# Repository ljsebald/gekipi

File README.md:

# GekiPi

A controller for games such as O.N.G.E.K.I. based around the Raspberry Pi Pico.

Please note that this is still a Work-In-Progress and isn't really meant for
anyone to actually try to use just yet.

## License

The code in the firmware directory is covered by the MIT License. See
`COPYING.MIT` for more information.

The hardware design in the board directory is covered by the CERN Open Hardware
License Version 2 - Strongly Reciprocal (CERN-OHL-S). See `cern_ohl_s_v2.txt`
for more information.

## Dependencies

The firmware for GekiPi currently only depends on the base Raspberry Pi Pico
SDK, its TinyUSB library, and my version of pn532-lib (which is a git submodule
of the firmware directory).

## Pinouts and GPIO assignments:

Buttons (other than the WAD and Test/Service button) have the following pinout:
1. +5v
2. LED In
3. Signal (active low)
4. LED Out
5. GND

Test/Service have the following pinout:
1. Signal (active low)
2. GND

The WADs have the following pinout:
1. +5v
2. +3.3v
3. LED In
4. Signal (active high, +3.3v)
5. LED Out
6. GND

The NFC connector has the following pinout:
1. +5v
2. +3.3v
3. LED In
4. SDA
5. SCL
6. GND

The Stick connector has the following pinout:
1. +3.3v
2. Analog Signal
3. Analog GND

The LEDs are wired in the following order (all are single LEDs except the WADs):
1. Left Red
2. Left Green
3. Left Blue
4. Right Red
5. Right Green
6. Right Blue
7. Left Menu
8. Right Menu
9. Left WAD
10. Right WAD
11. NFC

The number of LEDs per WAD can be set in the code and defaults to 6.

GPIO pins are assigned as follows on the Pico:
- GPIO0: Left Red
- GPIO1: Left Green
- GPIO2: Left Blue
- GPIO3: Right Red
- GPIO4: Right Green
- GPIO5: Right Blue
- GPIO6: Left Menu
- GPIO7: Right Menu
- GPIO8: Left WAD
- GPIO9: Right WAD
- GPIO16: NFC SDA
- GPIO17: NFC SCL
- GPIO20: LED Output (to 74AHCT125, then Left Red)
- GPIO21: Service
- GPIO22: Test
- GPIO28/ADC2: Stick

All other ADC channels available on a standard Pi Pico board are wired to the
Analog connector (along with +3.3v and Analog GND).

All other GPIO pins (other than those on the Analog connector) are available on
the GPIO connector (along with +3.3v, +5v, and GND)

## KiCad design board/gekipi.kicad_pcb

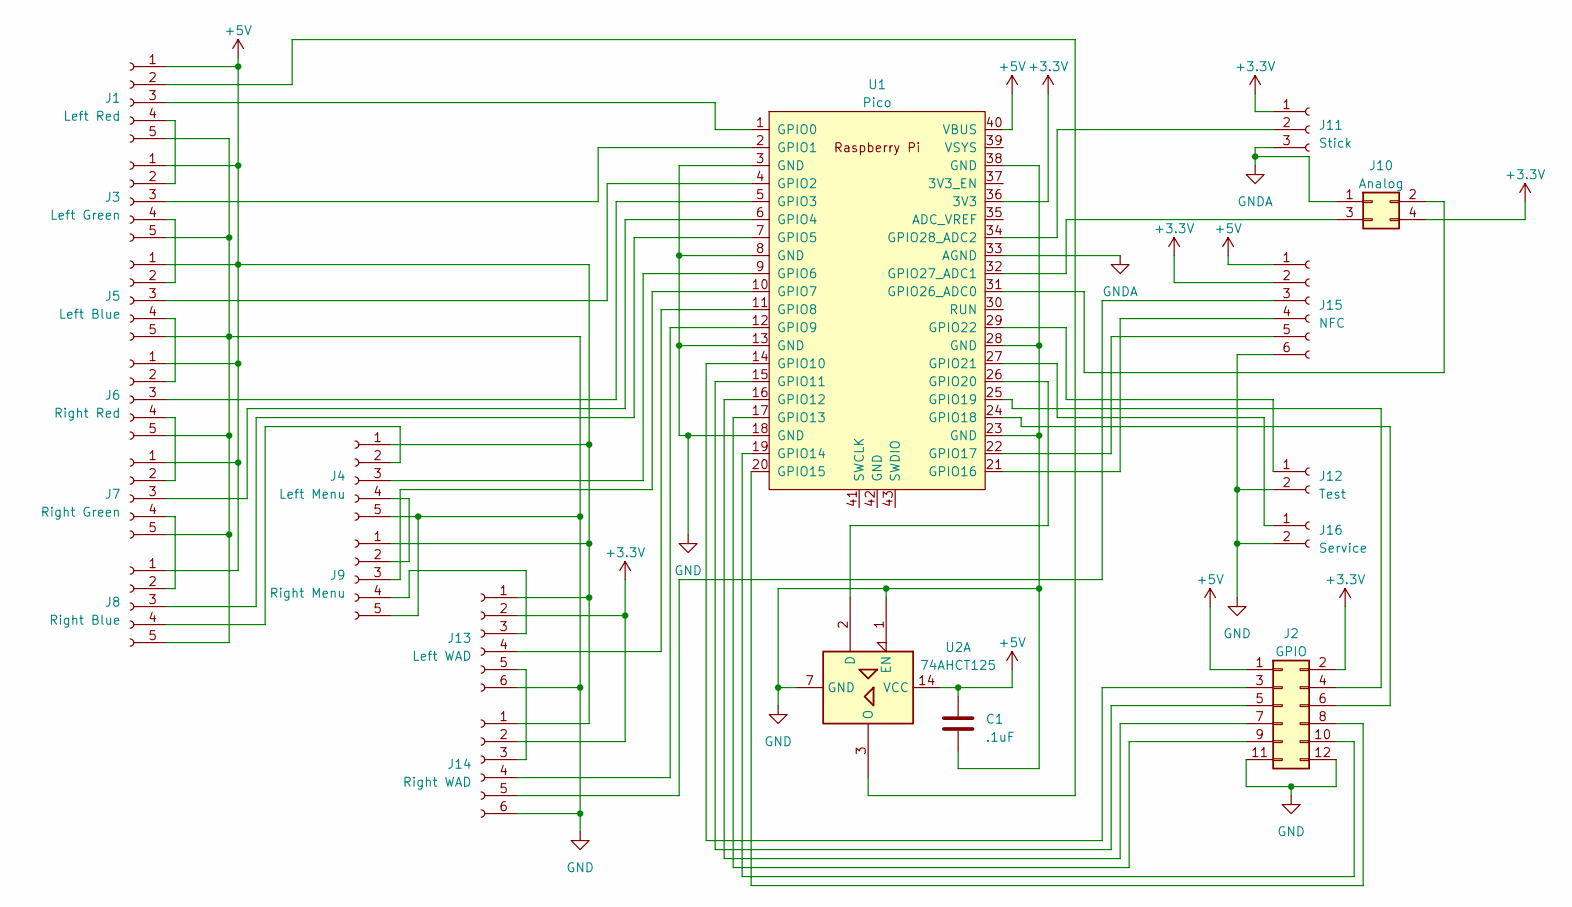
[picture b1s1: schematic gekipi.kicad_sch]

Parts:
C1: .1uF; C_Rect_L4.0mm_W2.5mm_P2.50mm
J1: Left Red; JST_XH_B5B-XH-A_1x05_P2.50mm_Vertical
J2: GPIO; PinHeader_2x06_P2.54mm_Vertical
J3: Left Green; JST_XH_B5B-XH-A_1x05_P2.50mm_Vertical
J4: Left Menu; JST_XH_B5B-XH-A_1x05_P2.50mm_Vertical
J5: Left Blue; JST_XH_B5B-XH-A_1x05_P2.50mm_Vertical
J6: Right Red; JST_XH_B5B-XH-A_1x05_P2.50mm_Vertical
J7: Right Green; JST_XH_B5B-XH-A_1x05_P2.50mm_Vertical
J8: Right Blue; JST_XH_B5B-XH-A_1x05_P2.50mm_Vertical
J9: Right Menu; JST_XH_B5B-XH-A_1x05_P2.50mm_Vertical
J10: Analog; PinHeader_2x02_P2.54mm_Vertical
J11: Stick; JST_XH_B3B-XH-A_1x03_P2.50mm_Vertical
J12: Test; JST_XH_B2B-XH-A_1x02_P2.50mm_Vertical
J13: Left WAD; JST_XH_B6B-XH-A_1x06_P2.50mm_Vertical
J14: Right WAD; JST_XH_B6B-XH-A_1x06_P2.50mm_Vertical
J15: NFC; JST_XH_B6B-XH-A_1x06_P2.50mm_Vertical
J16: Service; JST_XH_B2B-XH-A_1x02_P2.50mm_Vertical
U1: Pico; RPi_Pico_SMD_TH
U2: 74AHCT125; DIP-14_W7.62mm

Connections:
+3.3V: J2.2, J10.4, J11.1, J13.2, J14.2, J15.2, U1.36 (3V3)
+5V: C1.1, J1.1, J2.1, J3.1, J4.1, J5.1, J6.1, J7.1, J8.1, J9.1, J13.1, J14.1, J15.1, U1.40 (VBUS), U2.14 (VCC)
GND: C1.2, J1.5, J2.11, J2.12, J3.5, J4.5, J5.5, J6.5, J7.5, J8.5, J9.5, J12.2, J13.6, J14.6, J15.6, J16.2, U1.3 (GND), U1.8 (GND), U1.13 (GND), U1.18 (GND), U1.23 (GND), U1.28 (GND), U1.38 (GND), U2.1 (EN), U2.7 (GND)
GNDA: J10.1, J11.3, U1.33 (AGND)
unnamed: J1.2, U2.3 (O)
unnamed: J1.3, U1.1 (GPIO0)
unnamed: J1.4, J3.2
unnamed: J2.3, U1.14 (GPIO10)
unnamed: J2.4, U1.25 (GPIO19)
unnamed: J2.5, U1.15 (GPIO11)
unnamed: J2.6, U1.24 (GPIO18)
unnamed: J2.7, U1.16 (GPIO12)
unnamed: J2.8, U1.20 (GPIO15)
unnamed: J2.9, U1.17 (GPIO13)
unnamed: J2.10, U1.19 (GPIO14)
unnamed: J3.3, U1.2 (GPIO1)
unnamed: J3.4, J5.2
unnamed: J4.2, J8.4
unnamed: J4.3, U1.9 (GPIO6)
unnamed: J4.4, J9.2
unnamed: J5.3, U1.4 (GPIO2)
unnamed: J5.4, J6.2
unnamed: J6.3, U1.5 (GPIO3)
unnamed: J6.4, J7.2
unnamed: J7.3, U1.6 (GPIO4)
unnamed: J7.4, J8.2
unnamed: J8.3, U1.7 (GPIO5)
unnamed: J9.3, U1.10 (GPIO7)
unnamed: J10.2, U1.31 (GPIO26_ADC0)
unnamed: J10.3, U1.32 (GPIO27_ADC1)
unnamed: J11.2, U1.34 (GPIO28_ADC2)
unnamed: J12.1, U1.29 (GPIO22)
unnamed: J9.4, J13.3
unnamed: J13.4, U1.11 (GPIO8)
unnamed: J13.5, J14.3
unnamed: J14.4, U1.12 (GPIO9)
unnamed: J14.5, J15.3
unnamed: J15.4, U1.21 (GPIO16)
unnamed: J15.5, U1.22 (GPIO17)
unnamed: J16.1, U1.27 (GPIO21)
unnamed: U1.26 (GPIO20), U2.2 (D)

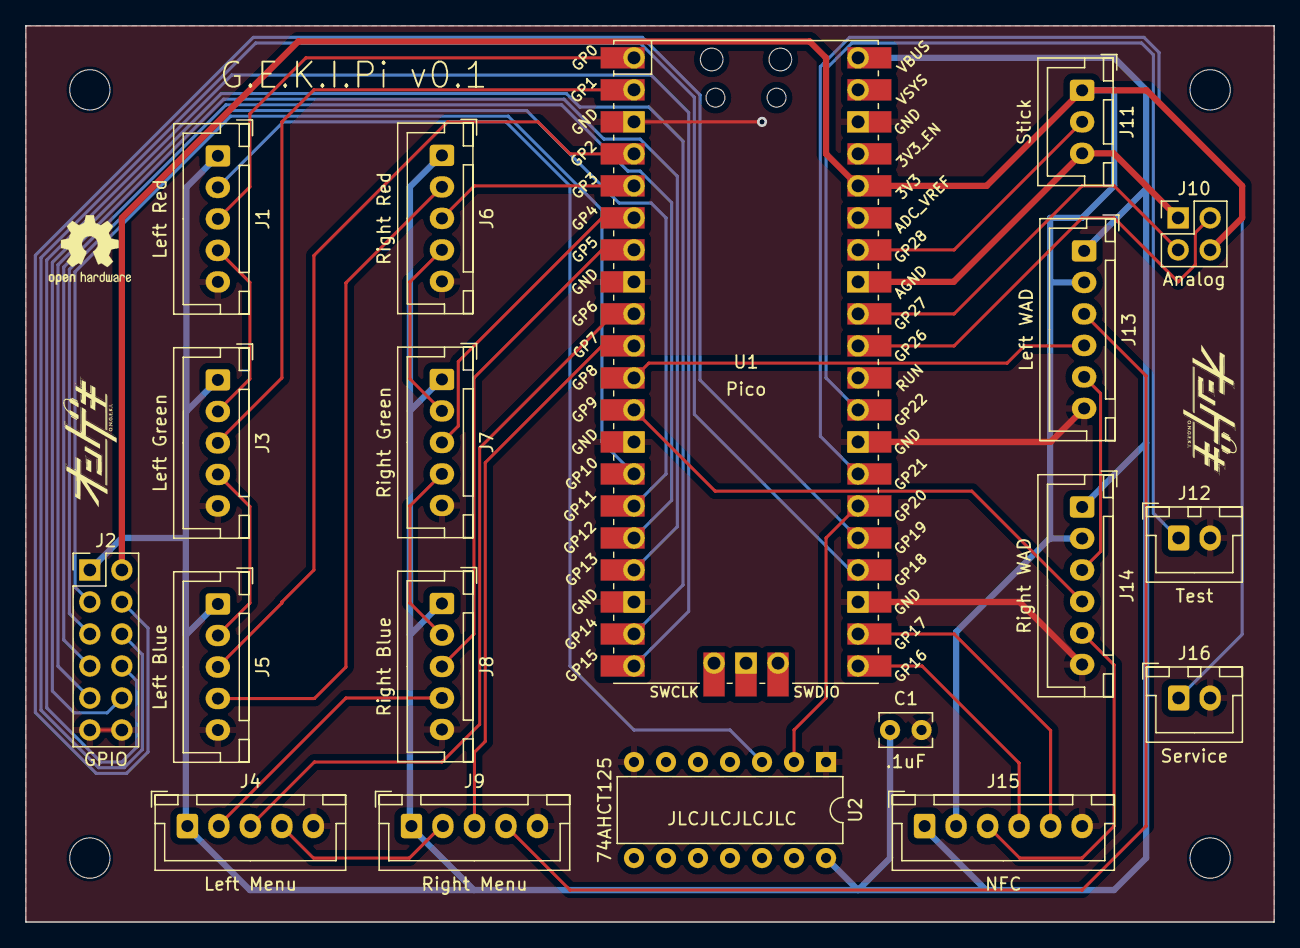
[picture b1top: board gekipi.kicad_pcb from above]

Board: 2 copper layers, 99.1 x 71.1 mm, 20 parts (1 on the bottom side), 41 nets.

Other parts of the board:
ongeki-back: LOGO

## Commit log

2023-03-04 Add stupidly simple initial firmware version for controller.
2023-06-02 Modify code to match GekiPi v0.1 board
2023-06-03 Add bitmap keyboard code
2023-06-03 Fix name of power supply mode pin
2023-06-03 Switch from 6KRO keyboard emulation to NKRO
2023-06-03 Add KiCad 7.0 project for PCB.
2023-06-03 Add license blob
2023-06-03 Add GPL license text
2023-06-03 Update README a bit...
2023-06-03 Document board layout for v0.1 board.
2023-06-05 Add CERN-OHL-S license.
2023-06-05 Add LICENSE
2023-06-08 Init LEDs.
2023-06-11 Add untested I/O for reading cards and setting LEDs.
2024-01-19 Import start of new non-python firmware.
2024-01-19 Fix formatting a bit.
2024-01-19 More correct HID descriptor for the controls.
2024-01-19 Add GPIO setup and gpio button reporting
2024-01-19 Call init_gpios() on startup
2024-01-19 Add stick reading
2024-01-19 License change for firmware to MIT
2024-01-19 Add code for communicating with LEDs.
2024-01-21 Add i2c setup.
2024-01-23 Set PID/VID.
2024-01-24 Add submodule for pn532-lib
2024-01-24 Add pn532 library into build.
2024-01-25 Add config for IRQ pin and switch from multicore fifo to a queue instead.
2024-01-27 Update pn532-lib
2024-02-05 Split nfc+led and controller functionality into two HID devices.
    Unfortunately, raw hid with multiple descriptors doesn't seem to work very well... So, we separate the two functions into separate hid devices here.
2024-02-05 Make NFC polling switch back and forth between mifare/felica and work.
2024-02-07 Set up api for reading NFC data back and such....
2024-02-10 Add command to rawhid device to fetch control data.
2024-02-10 Fix capitalization.
2024-02-15 Support inverted stick values and fix buttons that are inverted.
